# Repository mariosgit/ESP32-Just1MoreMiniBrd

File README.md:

# ESP32 minimal board

For use with one of these PRC Uart adapters...

# Status

Working.

Gerber files do not show (all?) the footprint labels on silkscreen ?

# Usage

Plug the FTDI thing in the 6 right pins on the FTDI header.
Also make a connection from RTS on the FTDI adapter to the remaining left pin of the FTDI header. You can also connect 5V from the FTDI board to the Vin pin. Put the voltage select jumper on the FTDI board to 3.3V.

Now the ESP32 should get power (measure to the right of the FTDI header)
And it should be programmable from Arduino or PlatformIO.

The numbers on the outer pinheaders refere to the GPIO numbers.

# Ref

Inspired by  [this thing](https://electronoobs.com/eng_arduino_tut172.php)

# License

MIT

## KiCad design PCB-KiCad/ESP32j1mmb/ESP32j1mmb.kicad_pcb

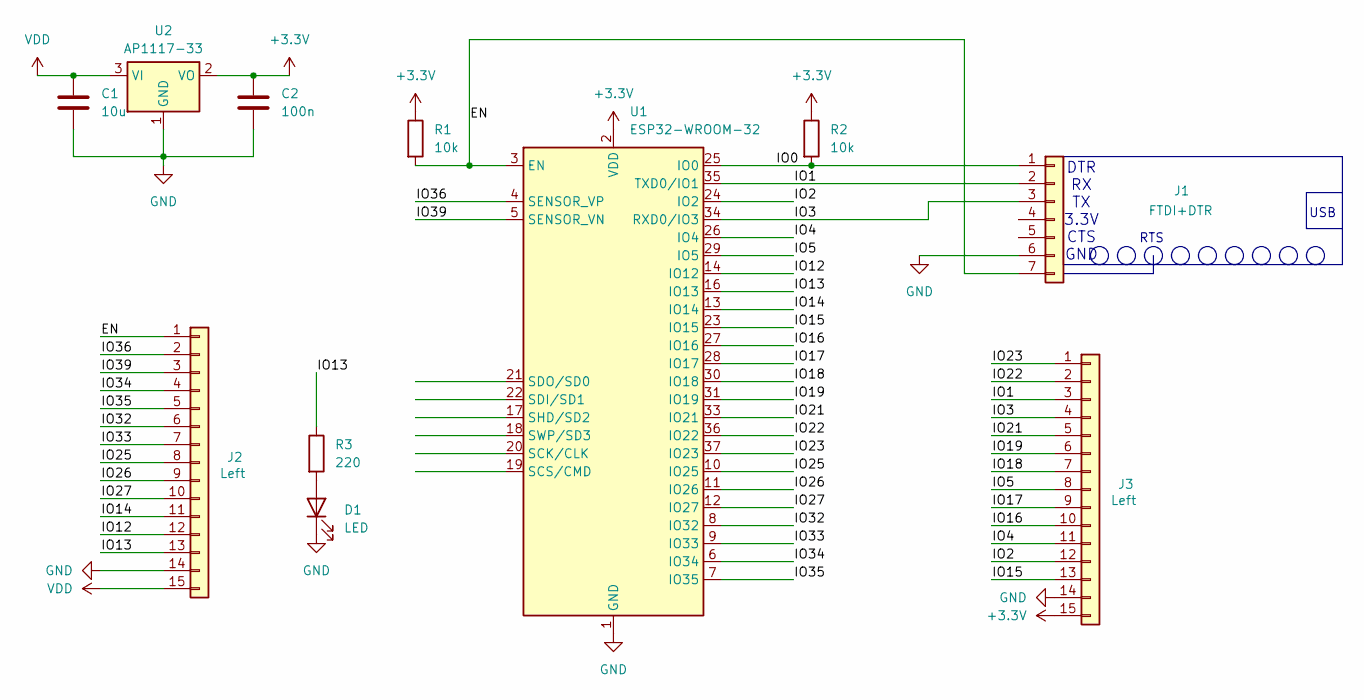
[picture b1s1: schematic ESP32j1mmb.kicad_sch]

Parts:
C1: 10u; C_0603_1608Metric_Pad1.08x0.95mm_HandSolder
C2: 100n; C_0603_1608Metric_Pad1.08x0.95mm_HandSolder
D1: LED; LED_0603_1608Metric_Pad1.05x0.95mm_HandSolder
J1: FTDI+DTR; PinHeader_1x07_P2.54mm_Vertical
J2, J3: Left; PinHeader_1x15_P2.54mm_Vertical
R1, R2: 10k; R_0603_1608Metric_Pad0.98x0.95mm_HandSolder
R3: 220; R_0603_1608Metric_Pad0.98x0.95mm_HandSolder
U1: ESP32-WROOM-32
U2: AP1117-33; SOT-223-3_TabPin2

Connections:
+3.3V: C2.1, J3.15, R1.1, R2.1, U1.2 (VDD), U2.2 (VO)
/EN: J1.7, J2.1, R1.2, U1.3 (EN)
/IO0: J1.1, R2.2, U1.25 (IO0)
/IO1: J1.2, J3.3, U1.35 (TXD0/IO1)
/IO2: J3.12, U1.24 (IO2)
/IO3: J1.3, J3.4, U1.34 (RXD0/IO3)
/IO4: J3.11, U1.26 (IO4)
/IO5: J3.8, U1.29 (IO5)
/IO12: J2.12, U1.14 (IO12)
/IO13: J2.13, R3.1, U1.16 (IO13)
/IO14: J2.11, U1.13 (IO14)
/IO15: J3.13, U1.23 (IO15)
/IO16: J3.10, U1.27 (IO16)
/IO17: J3.9, U1.28 (IO17)
/IO18: J3.7, U1.30 (IO18)
/IO19: J3.6, U1.31 (IO19)
/IO21: J3.5, U1.33 (IO21)
/IO22: J3.2, U1.36 (IO22)
/IO23: J3.1, U1.37 (IO23)
/IO25: J2.8, U1.10 (IO25)
/IO26: J2.9, U1.11 (IO26)
/IO27: J2.10, U1.12 (IO27)
/IO32: J2.6, U1.8 (IO32)
/IO33: J2.7, U1.9 (IO33)
/IO34: J2.4, U1.6 (IO34)
/IO35: J2.5, U1.7 (IO35)
/IO36: J2.2, U1.4 (SENSOR_VP)
/IO39: J2.3, U1.5 (SENSOR_VN)
GND: C1.2, C2.2, D1.1 (K), J1.6, J2.14, J3.14, U1.1 (GND), U1.15 (GND), U1.38 (GND), U1.39 (GND), U2.1 (GND)
unnamed: D1.2 (A), R3.2
VDD: C1.1, J2.15, U2.3 (VI)

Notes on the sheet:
USB
RTS
DTR RX TX 3.3V CTS GND

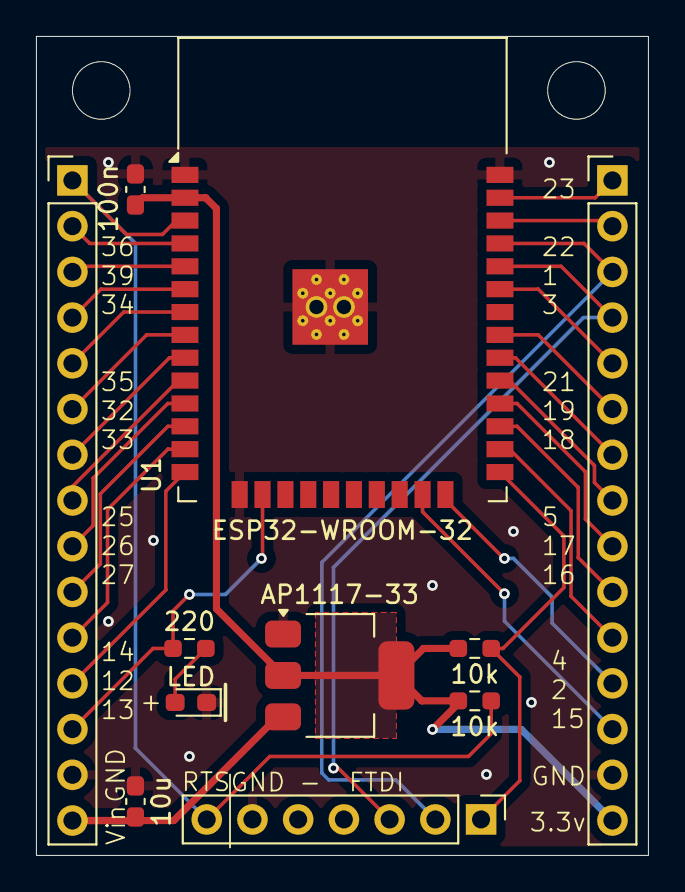
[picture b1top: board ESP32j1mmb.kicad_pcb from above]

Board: 2 copper layers, 34.0 x 45.5 mm, 11 parts (0 on the bottom side), 31 nets.

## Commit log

2024-02-25 Added Readme.
2024-02-25 Added Lic
2024-02-25 More readme...
2024-03-07 Experimented with silkscreen issues.. updated README.
2024-07-09 Added image.
